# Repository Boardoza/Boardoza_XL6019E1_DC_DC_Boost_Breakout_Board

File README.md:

# Boardoza XL6019E1  DC-DC Boost Converter Breakout Board

The **Boardoza XL6019E1** is a high-efficiency **DC-DC boost converter breakout board** built around the **XL6019E1** switching regulator IC. It is designed to step up low DC input voltages to higher, regulated output voltage levels while maintaining high efficiency and stable operation.

This board is well suited for **industrial electronics, robotics, LED drivers, automotive systems, battery-powered projects, and embedded applications** where higher voltage outputs such as 12V, 24V, 36V, or 48V are required from lower-voltage sources. Its compact size and simple pinout make it ideal for both prototyping and final product integration.

## [Click here to purchase!](https://www.ozdisan.com/ureticiler/boardoza)

| Front Side | Back Side |
|:---:|:---:|
|  |  |

---

## Key Features

- **Wide Input Voltage Range:** Supports input voltages from **5V to 40V**, allowing operation from a wide variety of DC power sources.
- **Selectable Output Voltage Levels:** Provides regulated, selectable output voltages of **12V, 24V, 36V, or 48V** to suit different system requirements.
- **High-Efficiency Boost Conversion:** Designed for high performance with efficiency levels of up to **94%**, minimizing power loss.
- **Fixed Switching Frequency:** Operates at a stable **180 kHz switching frequency** for predictable and reliable behavior.
- **High Switching Current Capability:** Supports up to **5A internal switching current**, suitable for demanding boost applications.

---

## Technical Specifications

**Model:** XL6019E1  
**Manufacturer:** Boardoza  
**Manufacturer IC:** XLSEMI   
**Input Voltage:** 5V – 40V  
**Output Voltage:** 12V, 24V, 36V, 48V (Selectable)  
**Converter Type:** DC-DC Boost Converter  
**Maximum Output Current:** Up to 2A (depending on input voltage and operating conditions)  
**Switching Frequency:** 180 kHz  
**Maximum Switching Current:** 5A  
**Operating Temperature:** -40°C to +125°C  
**Board Dimensions:** 40 mm × 40 mm  

---

## Board Pinout

### **( J1 ) Input Connector**

| Pin Number | Pin Name | Description |
|:---:|:---:|---|
| 1 | VIN | Power Input (5V – 40V) |
| 2 | GND | Ground |

### **( J2 ) Output Connector**

| Pin Number | Pin Name | Description |
|:---:|:---:|---|
| 1 | VOUT | Boosted Output Voltage (12V / 24V / 36V / 48V) |
| 2 | GND | Ground |

---

## Board Dimensions

---

## Step Files

[Boardoza XL6019E1.step](./assets/XL6019E1%20Step.step)

---

## Datasheet

[XL6019E1 Datasheet.pdf](./assets/XL6019E1%20Datasheet.pdf)

---

## Version History

- V1.0.0 – Initial Release

---

## Support

- If you have any questions or need support, please contact **support@boardoza.com**

---

## **License**
### **Hardware Design**

[![CC BY-SA 4.0][cc-by-sa-shield]][cc-by-sa]

All hardware design files are licensed under [Creative Commons Attribution-ShareAlike 4.0 International License][cc-by-sa].

[cc-by-sa]: http://creativecommons.org/licenses/by-sa/4.0/
[cc-by-sa-shield]: https://img.shields.io/badge/License-CC%20BY--SA%204.0-lightgrey.svg

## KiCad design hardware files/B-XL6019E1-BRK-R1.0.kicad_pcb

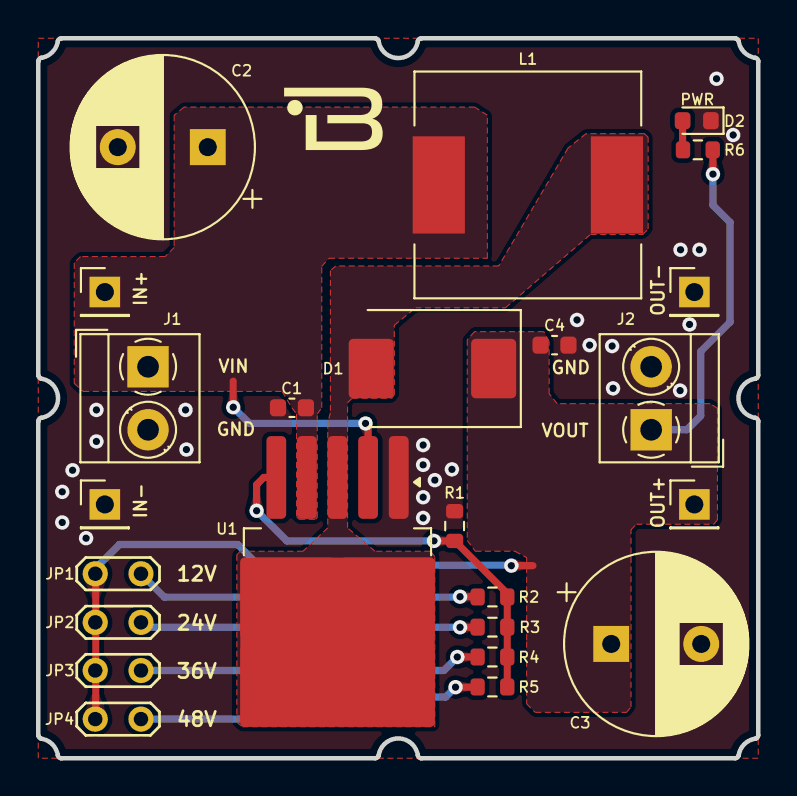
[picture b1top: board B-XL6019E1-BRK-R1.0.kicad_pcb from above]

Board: 2 copper layers, 40.0 x 40.0 mm, 24 parts (0 on the bottom side), 10 nets.

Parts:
C1, C4: 1uF; C_0603_1608Metric
C2, C3: 220uF; CP_Radial_D10.0mm_P5.00mm
D1: B560C-13-F; D_SMC
D2: LED; LED_0603_1608Metric
J1, J2: Screw_Terminal_01x02; TerminalBlock_MetzConnect_Type059_RT06302HBWC_1x02_P3.50mm_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
J3, J4, J5, J6: Conn_01x01_Pin; PinHeader_1x01_P2.54mm_Vertical
JP1, JP2, JP3, JP4: Jumper_2_Open; TestPoint_2Pads_Pitch2.54mm_Drill0.8mm
L1: 47uH/5A; L_12x12mm_H4.5mm
R1: 2K; R_0603_1608Metric
R2: 17.4K; R_0603_1608Metric
R3: 36.5K; R_0603_1608Metric
R4: 56K; R_0603_1608Metric
R5: 75K; R_0603_1608Metric
R6: 6.2K; R_0603_1608Metric
U1: XL6019E1; TO-263-5_TabPin3

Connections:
/FB: R1.1, R2.1, R3.1, R4.1, R5.1, U1.5 (FB)
/FBVOUT: C3.1, C4.1, D1.1 (K), J2.1, J6.1, JP1.2 (B), JP2.2 (B), JP3.2 (B), JP4.2 (B), R6.1
/VIN: C1.1, C2.1, J1.1, J4.1, L1.1, U1.2 (EN), U1.4 (VIN)
GND: C1.2, C2.2, C3.2, C4.2, D2.1 (K), J1.2, J2.2, J3.1, J5.1, R1.2, U1.1 (GND)
unnamed: D1.2 (A), L1.2, U1.3 (SW)
unnamed: D2.2 (A), R6.2
unnamed: JP1.1 (A), R2.2
unnamed: JP2.1 (A), R3.2
unnamed: JP3.1 (A), R4.2
unnamed: JP4.1 (A), R5.2
